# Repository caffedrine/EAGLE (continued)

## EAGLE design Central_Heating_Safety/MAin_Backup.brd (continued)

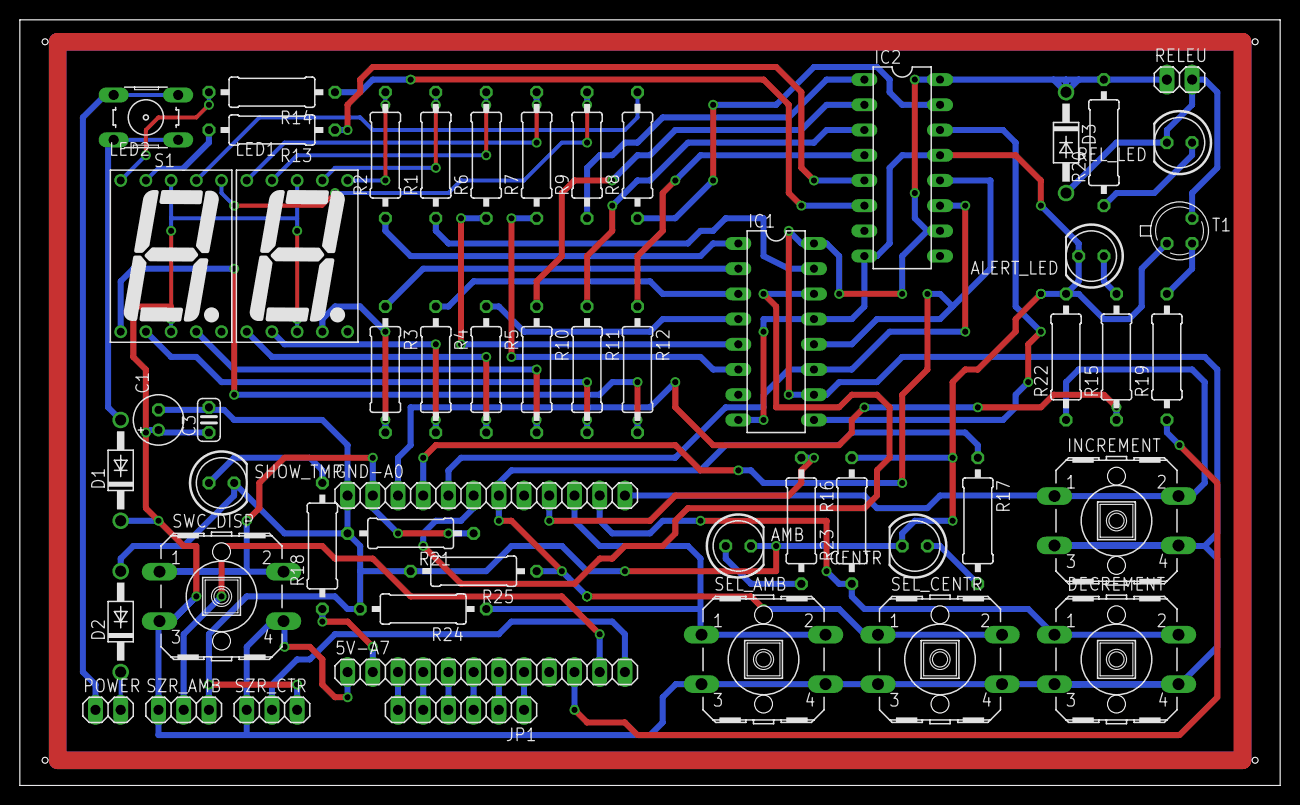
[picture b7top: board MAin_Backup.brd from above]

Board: 2 copper layers, 127.0 x 77.1 mm, 53 parts (0 on the bottom side), 61 nets.

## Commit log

2017-08-11 Added eagle projects
2017-08-11 First commit
    First commit
